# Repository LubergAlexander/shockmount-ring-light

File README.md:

# Description

LED Ring Light compatible with Blue Yeti Shockmount to re-use the microphone arm for the desk lamp/notification light.
Fits perfectly under the shockmount.

# Project structure

`hardware` - contains KiCAD project

`scripts` - python script to place LEDs & Capacitors in a ring. KiCAD needs to be compiled with Python support.

`images` - 3D render

# Pictures

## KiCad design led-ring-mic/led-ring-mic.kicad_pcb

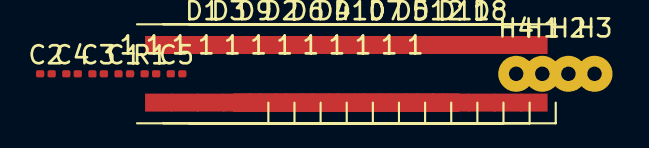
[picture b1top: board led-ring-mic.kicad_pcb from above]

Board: 2 copper layers, 22 parts (0 on the bottom side), 16 nets, no tracks yet.

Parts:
C1, C2, C3, C4, C5: 1uF; C_0201_0603Metric
D1, D2, D3, D4, D5, D6, D7, D8, D9, D10, D11, D12: WS2812B; LED_WS2812B_PLCC4_5.0x5.0mm_P3.2mm
H1: PWR; SolderWirePad_1x01_Drill0.8mm
H2: INPUT; SolderWirePad_1x01_Drill0.8mm
H3: GND; SolderWirePad_1x01_Drill0.8mm
H4: OUTPUT; SolderWirePad_1x01_Drill0.8mm
R1: 470; R_0201_0603Metric

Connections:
GND: C1.2, C2.2, C3.2, C4.2, C5.2, D1.3, D2.3, D3.3, D4.3, D5.3, D6.3, D7.3, D8.3, D9.3, D10.3, D11.3, D12.3, H3.1
unnamed: D1.2, D2.4
unnamed: D1.4, R1.1
unnamed: D2.2, D3.4
unnamed: D3.2, D4.4
unnamed: D4.2, D5.4
unnamed: D5.2, D6.4
unnamed: D6.2, D7.4
unnamed: D7.2, D8.4
unnamed: D8.2, D9.4
unnamed: D10.2, D11.4
unnamed: D9.2, D10.4
unnamed: D11.2, D12.4
unnamed: D12.2, H4.1
unnamed: H2.1, R1.2
VDD: C1.1, C2.1, C3.1, C4.1, C5.1, D1.1, D2.1, D3.1, D4.1, D5.1, D6.1, D7.1, D8.1, D9.1, D10.1, D11.1, D12.1, H1.1

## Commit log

2018-11-26 First drafts
2019-02-04 cleanup
2019-02-04 Restructure
2019-02-04 Added KiCAD scripts
2019-02-04 moved out of kicad project
2019-02-04 Pics
2019-12-10 Rename .yml to ci.yml
2019-12-10 debugging actions
2019-12-10 Added PDF generation
